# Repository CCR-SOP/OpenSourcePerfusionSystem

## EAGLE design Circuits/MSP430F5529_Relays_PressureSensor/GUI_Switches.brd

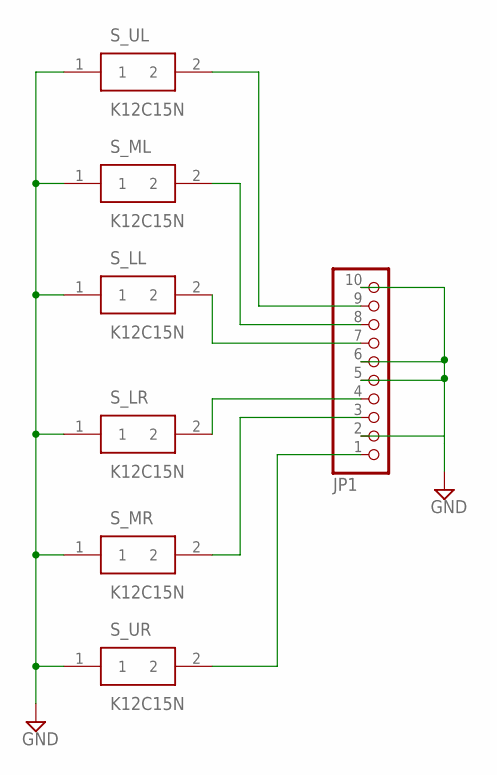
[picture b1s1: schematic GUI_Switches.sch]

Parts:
JP1: PINHD-1X10/90; 1X10/90
S_LL: K12C15N
S_LR: K12C15N
S_ML: K12C15N
S_MR: K12C15N
S_UL: K12C15N
S_UR: K12C15N

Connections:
GND: JP1.2, JP1.5, JP1.6, JP1.10, S_LL.1, S_LR.1, S_ML.1, S_MR.1, S_UL.1, S_UR.1
unnamed: JP1.7, S_LL.2
unnamed: JP1.9, S_UL.2
unnamed: JP1.4, S_LR.2
unnamed: JP1.3, S_MR.2
unnamed: JP1.1, S_UR.2
unnamed: JP1.8, S_ML.2

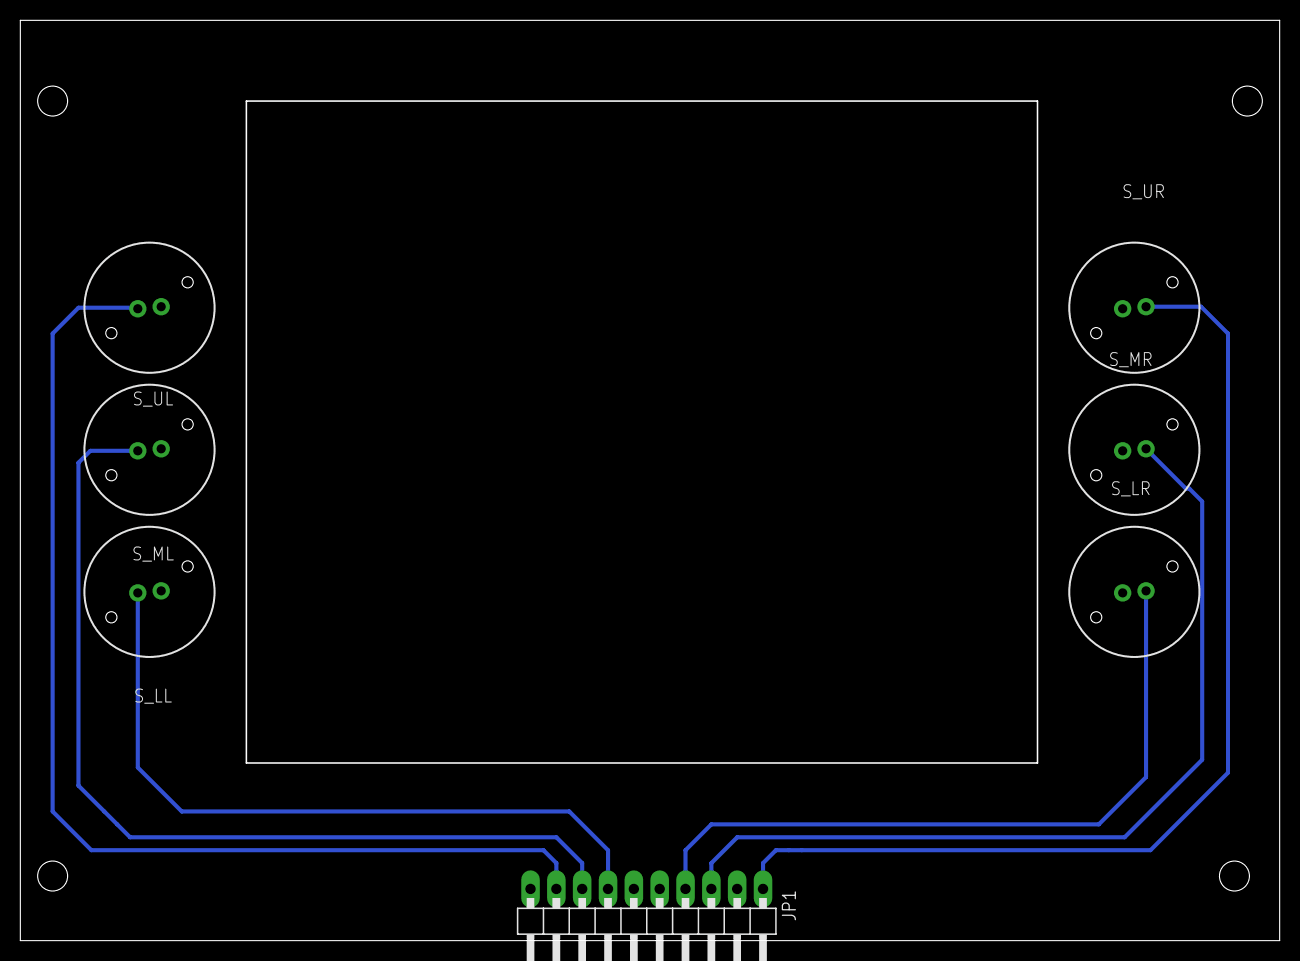
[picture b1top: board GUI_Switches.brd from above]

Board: 2 copper layers, 123.8 x 90.5 mm, 7 parts (0 on the bottom side), 7 nets.

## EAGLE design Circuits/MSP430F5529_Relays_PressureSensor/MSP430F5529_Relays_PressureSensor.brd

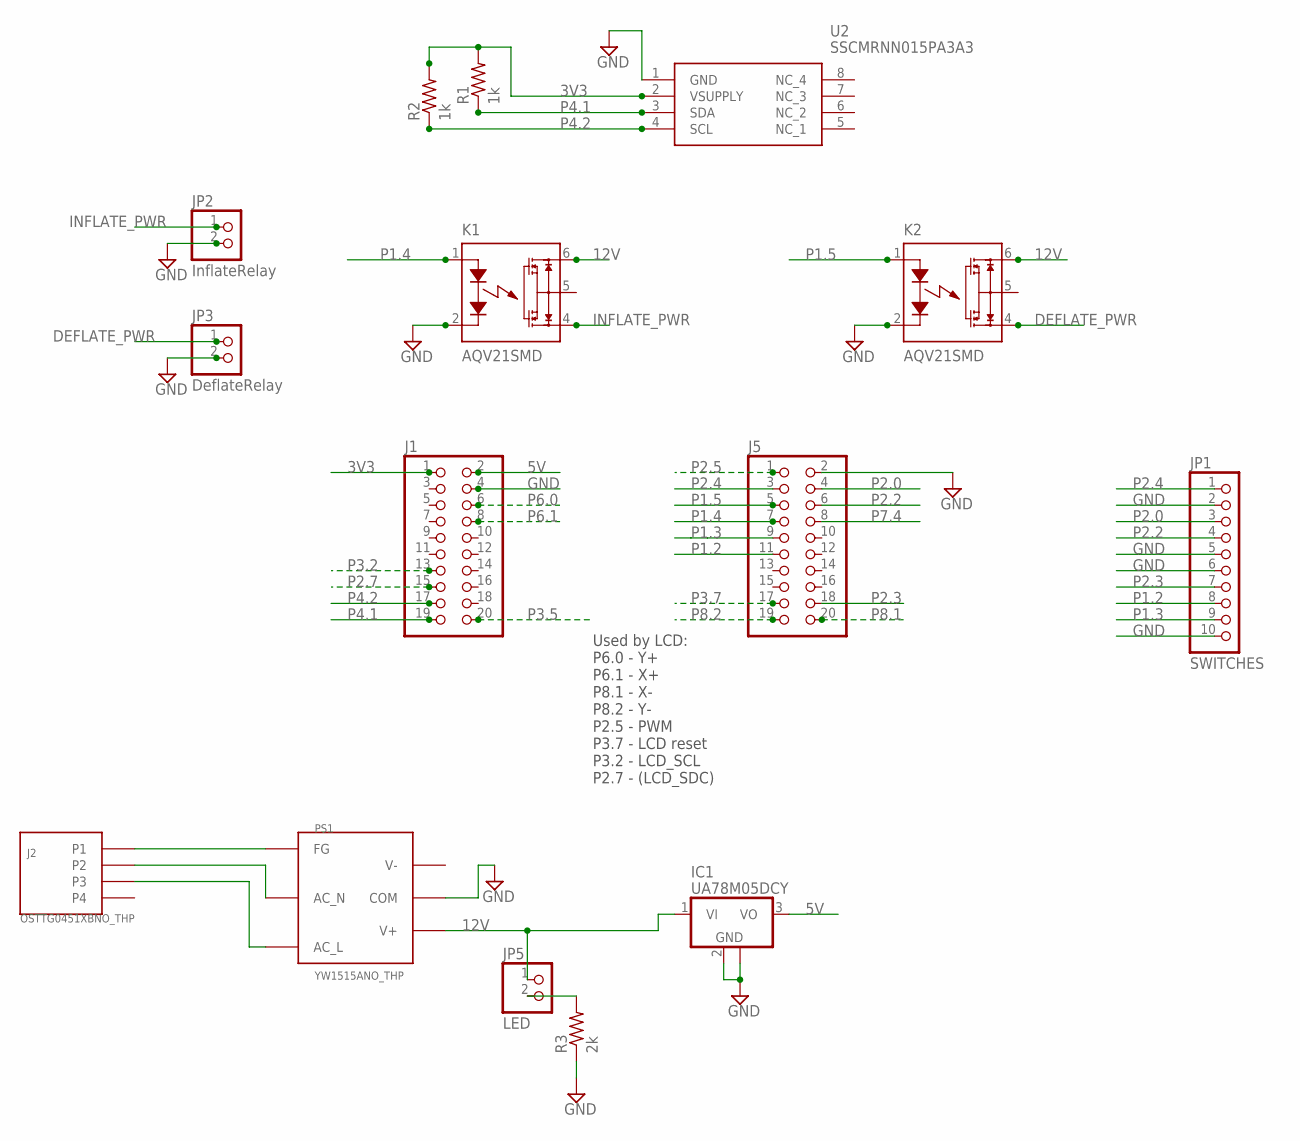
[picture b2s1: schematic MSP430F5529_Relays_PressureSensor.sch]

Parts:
IC1: UA78M05DCY; SOT223
J1, J5: PINHD-2X10; 2X10
J2: OSTTG0451XBNO_THP; TERM_4PIN_5.08MM_NO_THP
JP1: SWITCHES; 1X10/90
JP2: InflateRelay; 1X02/90
JP3: DeflateRelay; 1X02/90
JP5: LED; 1X02/90
K1, K2: AQV21SMD; DIL06SMD
PS1: YW1515ANO_THP; YW15_NO_THP
R1, R2: 1k; M1206
R3: 2k; M1206
U2: SSCMRNN015PA3A3; SOP254P1330X598-8N

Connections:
3V3: J1.1, R1.2, R2.2, U2.2 (VSUPPLY)
5V: IC1.3 (VO), J1.2
12V: IC1.1 (VI), JP5.1, K1.6 (D1), K2.6 (D1), PS1.P4 (V+)
AC_L: J2.P3, PS1.P3 (AC_L)
AC_N: J2.P2, PS1.P2 (AC_N)
DEFLATE_PWR: JP3.1, K2.4 (D2)
FG: J2.P1, PS1.P1 (FG)
GND: IC1.2 (GND), IC1.4 (GND), J1.4, J5.2, JP1.2, JP1.5, JP1.6, JP1.10, JP2.2, JP3.2, K1.2 (K), K2.2 (K), PS1.P5 (COM), R3.1, U2.1 (GND)
INFLATE_PWR: JP2.1, K1.4 (D2)
unnamed: JP5.2, R3.2
P1.2: J5.11, JP1.8
P1.3: J5.9, JP1.9
P1.4: J5.7, K1.1 (A)
P1.5: J5.5, K2.1 (A)
P2.0: J5.4, JP1.3
P2.2: J5.6, JP1.4
P2.3: J5.18, JP1.7
P2.4: J5.3, JP1.1
P2.5: J5.1
P2.7: J1.15
P3.2: J1.13
P3.5: J1.20
P3.7: J5.17
P4.1: J1.19, R1.1, U2.3 (SDA)
P4.2: J1.17, R2.1, U2.4 (SCL)
P6.0: J1.6
P6.1: J1.8
P7.4: J5.8
P8.1: J5.20
P8.2: J5.19
V-: PS1.P6 (V-)

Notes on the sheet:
Used by LCD: P6.0 - Y+ P6.1 - X+ P8.1 - X- P8.2 - Y- P2.5 - PWM P3.7 - LCD reset P3.2 - LCD_SCL P2.7 - (LCD_SDC)

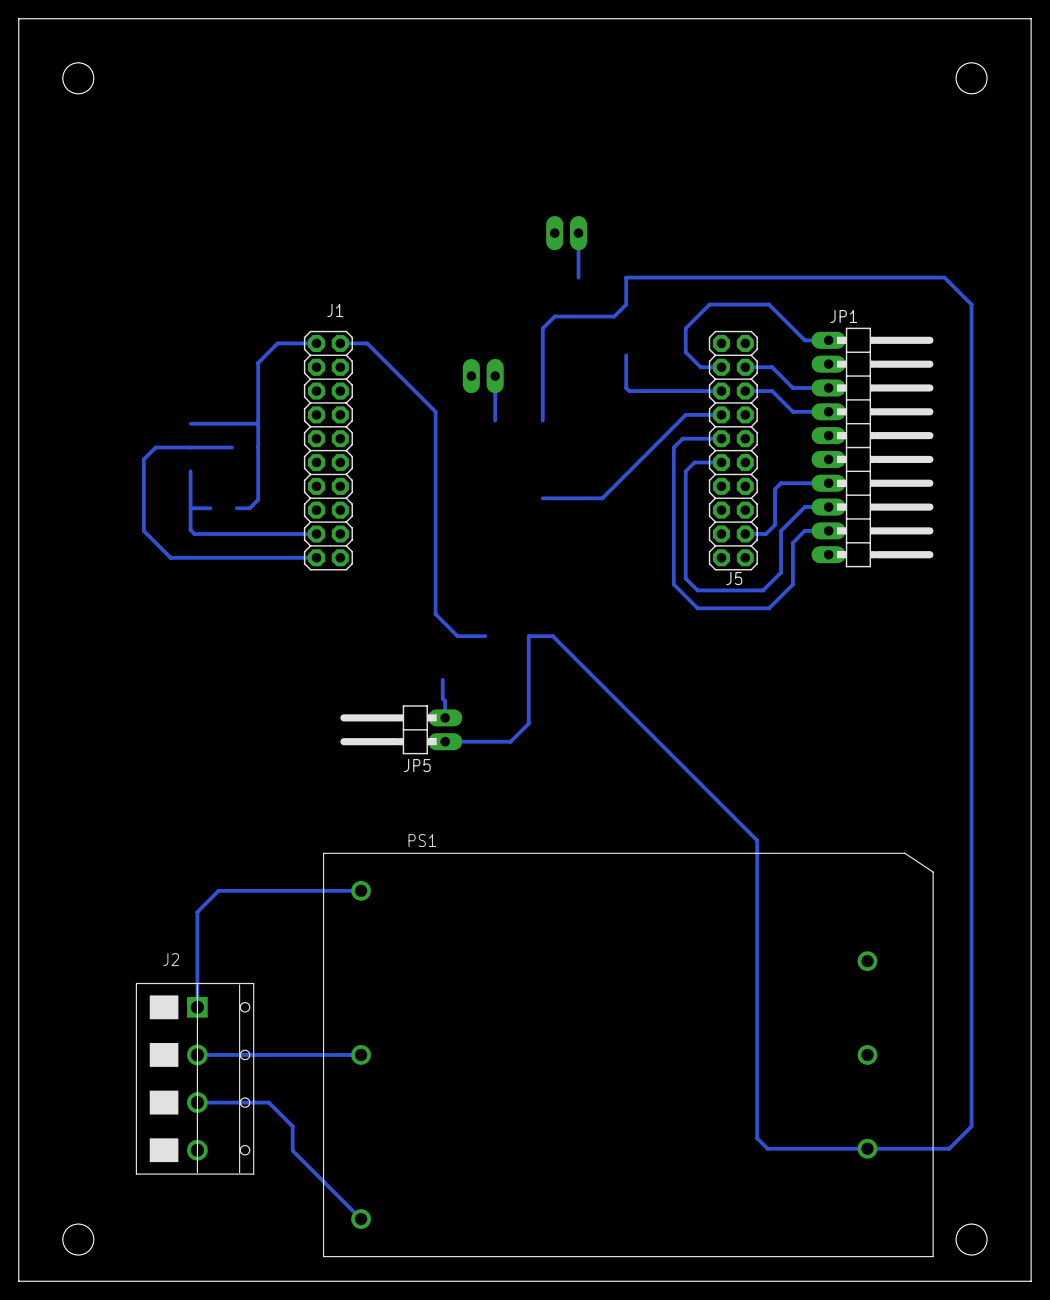
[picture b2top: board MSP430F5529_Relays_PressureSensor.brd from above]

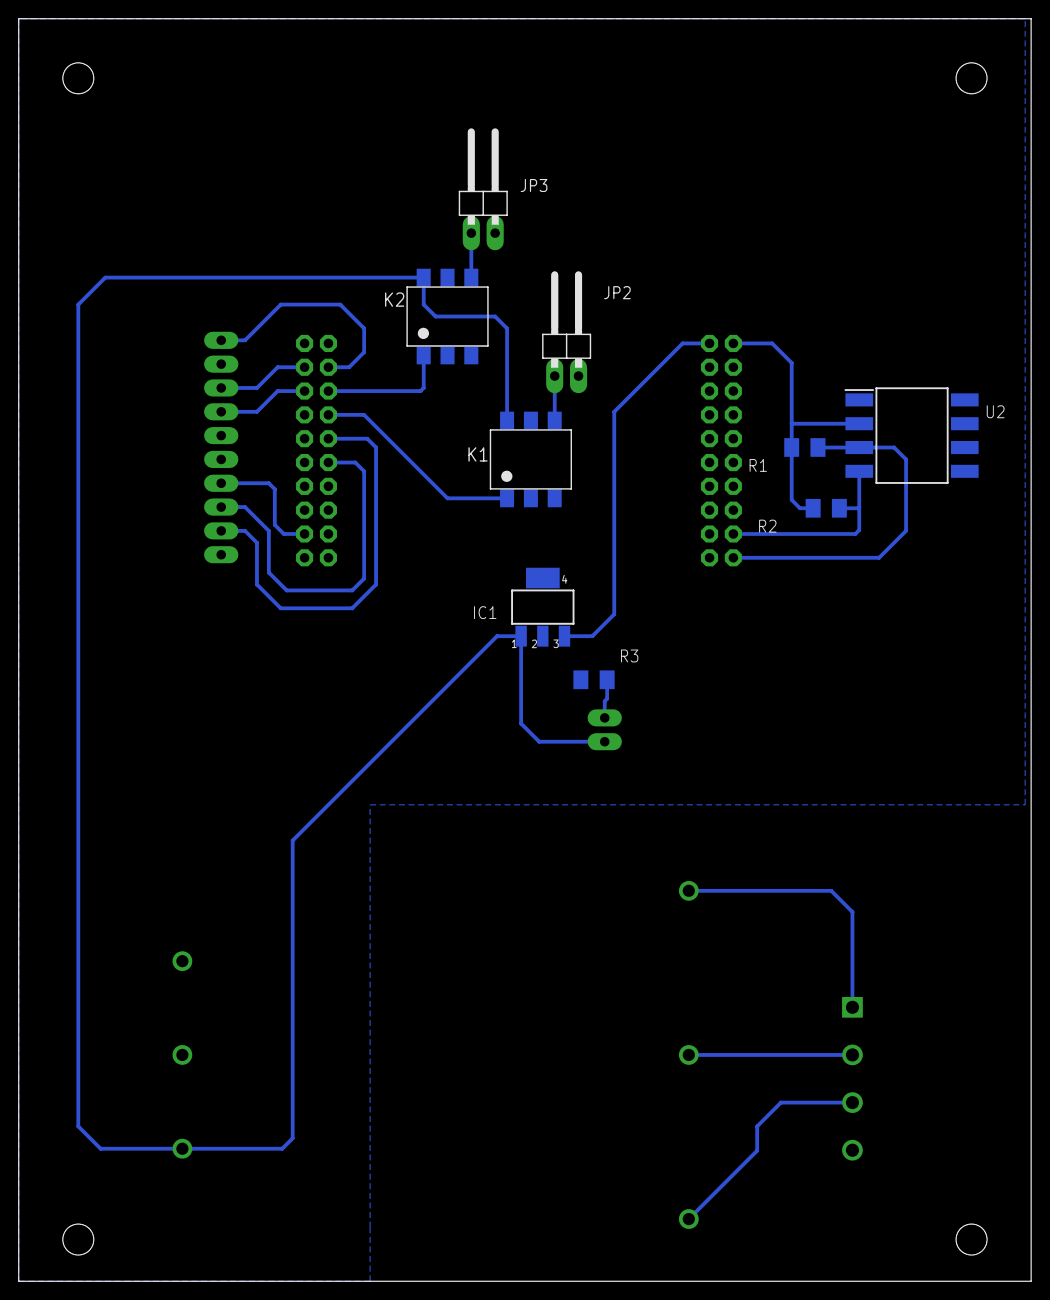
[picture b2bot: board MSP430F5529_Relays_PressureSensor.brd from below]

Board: 2 copper layers, 107.9 x 134.6 mm, 15 parts (9 on the bottom side), 20 nets.

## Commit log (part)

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2023-04-18 add PerfusionSystem class to manage sensors update apps/panel as needed
2023-04-18 add PerfusionSystem to panel_multiple_syringes, accept syringe_sensor directly
2023-04-18 cleanup apps for new PerfusionSystem
2023-04-18 move automation parameters to the automation config
2023-04-19 autoload dc pump automations
2023-04-19 add autoloading of syringe automations
2023-04-19 autocreate lists in perfusionconfig clean up some logging
2023-04-19 eliminate type checking for Sensor
2023-04-19 remove tightlayout which doesn't work anyway
2023-04-19 get volume by flow example running
2023-04-19 add logging helpers to filter log messages add example to show how to filter
2023-04-20 move read/write config from Sensor to PerfusionSystem and handle configs from there. Allow better control of config source and loading of objects
2023-04-20 fix apps to work with new code move all panels to a gui subfolder
2023-04-28 Updates after testing general_updates
2023-04-28 Added manual TPN and Zosyn syringes (under auto file for simplicity)
2023-04-28 Adding in initial values to syringe panel
2023-04-28 remove old pump docs and add Levitronix docs
2023-04-28 add simple example for Levitronix pump
2023-04-28 update panel and mocks for working example (w/o hardware)
2023-04-28 added flow control for PuraLev
2023-04-28 check for valid hw before trying to read modbus registers
2023-04-28 remove old code from merge
2023-04-28 fix bugs from merge
2023-05-01 Syringe panel takes starting values from config
2023-05-01 Added logging window, changed layout of syringe gui
2023-05-02 redo enclosure acrylic
2023-05-02 Adjusted starting values in panel_gas_mxiers
2023-05-02 Further parameter updates to automations.ini
2023-05-02 debugging dc pump errors
2023-05-02 Updates to syringe configs
2023-05-02 updates to help debug why DC pumps don't work in Hernandez lab
2023-05-02 add thread to read responses in the background
2023-05-02 Re-ordered pump configs
2023-05-03 New calibrations for each pump
2023-05-03 complete non-blocking calls...Pump11Elite does not always return something or returns a blank. Reduce serial timeout and always strip all \r and \n
2023-05-03 Update to logging level
2023-05-03 UPdated calibration - needs additional edits to work with timer
2023-05-03 handle case where sensor doesn't have any units
2023-05-03 minor code cleanups, fix all examples
2023-05-03 log AutoSyringe as well
2023-05-04 Naming update
2023-05-04 More gas mixer design changes
2023-05-04 Changes to dialysis calibration
2023-05-04 Calibration values are set inpyDC to Pump 3 values - works currently
2023-05-05 Updates to automation logging and timing
2023-05-05 Final dialysis calibration fix
2023-05-08 increase serial timeout to see if that resolves get_infusion_rate response being blank
2023-05-09 check if serial port open before getting infuson rate to avoid issue with the stop() trying to record a continuous infusion stop on a closed port
2023-05-09 remove extra debug logging
2023-05-09 remove propagate=False in create_wx_handler as that blocks regular logging Update panel_gas_mixers for correct names to prevent duplicate messages
2023-05-09 don't enable flow when changing parameters unless it is already on
2023-05-09 Updated messaging in vasoactive automation
2023-05-10 code cleanup and better error checking return None when requesting data from syringe and the response is bad
2023-05-11 strip cr from str2send to prevent overwriting line in log file tested raising uncaught exception to verify crashes
2023-05-11 consistent use of super().__init__() all wxpython objects are saved to self (reaction to occasional exception thrown on Hernandez laptop about a deleted text control). Should ensure no object are del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
2023-05-11 remove hardware check for syringe status to see if that is causing errors
2023-05-12 consistent use of logger.exception()
2023-05-12 Logging level to INFO
2023-05-12 Removed counter from panel_Dialysis_ump
2023-05-16 Updates to automation
2023-05-17 Changes to automation during test run
2023-05-18 add gui for updating automation config
2023-05-22 Added 1.5 V ceiling for dialysis pumps to limit flow
2023-05-22 Pressure range in epo/phenyl automation to stop injection at midpoint
2023-05-23 updates to get pump working
2023-05-23 Removed restart when changing gas mixer percentage
2023-05-23 Added algorithm to increase flow in event of low O2 in arterial gas mixer
2023-05-23 do not add any vars by default for use in other automations adjust_rate needs to accept decimals
2023-05-23 shorten config button names reduce pH increment
2023-05-23 add gas mixer config gui
2023-05-24 Revert "shorten config button names"
    This reverts commit 829561172631b7fc14698520aae191e1fd1b8799.
2023-05-24 Revert "add vaso automation"
    This reverts commit e4363121003b70a794605d88203e65b8ecf66525.
2023-05-24 Initial Levitronix app framework
2023-05-24 Levitronix gui, configs updated to control both pumps
2023-05-24 updates to the layout, convert remaining ranges to individual variables
2023-05-24 add code for CITSens glucose sensor
2023-05-24 add classes and example for glucose sensor
2023-05-31 reorg panel_gas_mixers for more compact layout
2023-06-01 move automation config to buttons line remove <br> in log files so lines are more compact move logs and automation to basemixerpanel
2023-06-01 in log, search for sensor name, not hw name
2023-06-01 redo syringe panel control for more compact layout
2023-06-01 gas mixer panel minor cleanup
2023-06-02 enable syringe buttons
2023-06-02 update manual control layout for better fit
2023-06-02 adjust config gui elements for better fit on laptop resolution
2023-06-02 update to dialysis panel
2023-06-02 add LeviFlow_manual
2023-06-22 Example for hannah!
2023-06-22 Deleted extra syringe debugging
2023-06-22 Fixed levitronix logging error
2023-06-22 Removed flow view from levitronix panel
2023-06-22 Standardized logging display
2023-06-29 made dialysis pump layout three across, more condensed
2023-06-29 spread things out a bit more
2023-06-30 now when we stop flow in dialysis pumps the offset value goes back to zero
2023-07-21 BUGFIX: add missing lgr to BaseGasMixerPanel
2023-07-21 If nothing read from serial port, do not try to parse response
2023-07-26 BUGFIX: in arterial gas automation, if check for ph<min, and decrease CO2, ph>max, increase CO2
2023-08-09 add app to read existing file. Add functions to retrieve all data from a file
2023-08-09 get start timestamp from txt file minor code cleanups
2023-08-09 add support for points files
2023-08-10 move util functions to Strategy_ReadWrite, autocreate sensor based on output_type
2023-08-10 ensure sampling period saved to txt file
2023-08-14 refactor out creation of filename from parts
2023-08-14 add app to mass convert files
2023-08-14 for an AI channel, use the device's acq_start_ms minor code cleanups
2023-08-14 Changed venous gas mixer automation to turn on or off depending on PO2 reading. Made "flow_cancel" and "flow_resume" functions (parallel purpose to flow_adjust)
2023-08-18 specify date on command line
2023-08-18 add automation class for controlling flow
2023-08-21 add examples to test sinusoidal output and pid
2023-08-21 changed config file for HA gas control
2023-08-21 save change to Puralev speed ensure controls are updated with correct tunings
2023-08-22 update config files
2023-08-22 pid returns relative change, convert to absolute value
2023-08-23 integrate new waveform generation method
2023-08-23 if error loading a missing sensor/automation/etc., give more descriptive error message
2023-08-29 enable/disable controls based on sine output
2023-08-29 rename AutomationConfig to more generic ConfigGUI
2023-08-29 fix gui layout, link in config save/loading
2023-08-29 Create c clamp for holding acrylic to pan, update pan LxW, update acrylic LxW
2023-08-29 in retrieve_buffer, when retrieving data from memory-mapped file, use the len(data) instead of file_size as there is sometimes discrepancies.
2023-08-31 update to gui so buttons reflect actual status of pumps and automation remove debug statements
2023-08-31 use bpm instead of freq
2023-09-05 fix c clamp mirror, replace trap door hinge with hinge from lab and hw from lab
2023-09-06 minor visual updates
2023-09-12 update threading on pan drain adapter to make opening larger
2023-09-14 make tie bars v and h doubles
2023-09-21 make tie down bar holes through holes for V and H and shorten shank length on lock
2023-09-26 Add holes for tie bars on tubing panel. Update to 08 drain and adapter
2023-09-29 updated config files to fix error
2023-10-03 Add gaskets to trap doors and update lock
2023-10-05 Update diaphram metal to reduce file size and increase hole size
2023-10-18 Models for table components, pump, flow sensor, screen, peg board
2023-10-20 Clamp on flow sensor and holder work, radii and thru holes for gas ex
2023-10-24 updates to get Keyence flow sensors working fixes so Levitronix pumps start/stop correctly
2023-10-25 Update asm to reduce size
2023-10-30 Switch trap door trim, add hd filter, switch to double peg board hook
2023-11-06 Update peg board for irl depth and peg board holders
2023-11-09 Create loop for gas exchanger, hd filter thickness options
2023-11-15 update to valid range handling to reduce memory leaks
2023-12-07 add pressure sensor datasheets
2023-12-12 Update trap door hinge holes from 10-32 to 8-32 like irl
2023-12-15 update baud rate for CITSens glucose sensor
2024-01-08 update timeout of NIDAQ acq to be based on samples being read instead of independent timeout value
2024-01-08 show plots in relative time, not absolute
2024-01-08 BUGFIX: fix display of CITsens
2024-01-16 Clamp on pressure sensor table top asm, diaphragm in unit clip 
2024-02-27 fixed start/stop buttons and confirmed it worked with actual pumps
2024-02-28 fixed issue/error with start/stop buttons for dropdown drug infusions
2024-02-28 added panel for solumed - this now uses the old glucagon syringe pump, changed old glucagon syringe to 10mL (not coded)
2024-02-28 changed config for vasocontrict/dilate -- phenyl and epo were listed backwards
2024-02-28 drug drop downs initialize expanded
2024-02-28 A few aesthetic changes and color code for action/auto clicked/unclicked buttons so easier to visualize what settings are on
2024-03-07 changed auto gas so it doesn't read "zero" as past flow on flow_resume - which was just keeping the flow zero forever
2024-04-09 optimze the reading of the data file during conversion
2024-04-10 BUGFIX: start_ts also needs to be divided by 1000 to generate correct timestamp
2024-04-22 basic code for MCC AI, not completed or tested
2024-04-24 updates for working code
2024-04-25 cleanup example for multiple plots
2024-04-26 add additional error checking improve handling of buffers to avoid lost buffers fix bug in setting rate (was setting period, needed to specify samples/s)
2024-04-26 add error handling to catch invalid fid on close. Caused by calculated sensors using strategy outputs that were not created
2024-04-29 allow user to select which reader is displayed
2024-05-02 add basic code for controlling Nucleo DACs
2024-05-09 add board for Nucleo to ADC
2024-05-10 create board and enclosure for Nucleo DAC
2024-05-28 updated plotting code to use animations and clean up interface
2024-05-29 update code to work with multiple readers
2024-05-29 update code to new API
2024-06-07 remove .metadata folder from version control
2024-07-01 add mcculw to pipfile
2024-07-02 stop animation before closing plot
2024-07-02 add more code to ensure a proper shutdown of hardware, particularly MCC board. If not shutdown properly, the next time the code is run, the MCC board does not seem to acquire data
2024-08-05 remove old docs move all manuals/datasheets into one folder
2024-11-05 Create PostPerfusionAnalysisOverView
    made new folder for matlab
2024-11-05 Rename Master Data Sheet 20210406 to 20240730.xlsx to Master Data Sheet 2021 Thru 2023
2024-11-18 remove unsed circuits
2024-11-19 Delete System Setup/HOW TO Set Up Circuit for Liver Perfusion.pdf
    will re-add when updated
